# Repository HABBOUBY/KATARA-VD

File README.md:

<div align="center">

# KATARA-VD

### une mahcine qui ne vend pas mais elle donne

Built by **HABBOUBY EDEM**

</div>

---

## Table of Contents

- [About](#about)
- [Repository Structure](#repository-structure)
- [Scope of This Submission](#scope-of-this-submission)
- [Note on Physical Fabrication](#note-on-physical-fabrication)
- [The Story Behind KATARA-VD](#the-story-behind-katara-vd)
- [The Ecosystem: 2 Systems, 1 Mission](#the-ecosystem-2-systems-1-mission)
- [Vending Machine](#vending-machine)
  - [Part 1 — Skeleton, Shelving & Archimedean Dispensers](#part-1--skeleton-shelving--archimedean-dispensers)
  - [Part 2 — Solar Power & Access Doors](#part-2--solar-power--access-doors)
  - [Part 3 — Prescription Verification System](#part-3--prescription-verification-system)
  - [Part 4 — Coin Dispensing Mechanism ("Giving Money")](#part-4--coin-dispensing-mechanism-giving-money)
  - [Part 5 — Coin Acceptance & Storage](#part-5--coin-acceptance--storage)
  - [Part 6 — Charity Keypad PCB](#part-6--charity-keypad-pcb)
  - [Part 7 — Thermal Sensing & Voice Interaction](#part-7--thermal-sensing--voice-interaction)
- [JALOUL — The Restocking Humanoid](#jaloul--the-restocking-humanoid)
  - [Part 8 — Head & Expression System](#part-8--head--expression-system)
  - [Part 9 — Body & Shoulder Joints](#part-9--body--shoulder-joints)
  - [Part 10 — Arm Completion & 360° Gripper](#part-10--arm-completion--360-gripper)
  - [Part 11 — Mecanum Base & Vertical Lift](#part-11--mecanum-base--vertical-lift)
  - [Part 12 — Frame Reinforcement & LiDAR](#part-12--frame-reinforcement--lidar)
- [The Humanitarian Logic — How the Community Fund Works](#the-humanitarian-logic--how-the-community-fund-works)
- [Electronics & PCB](#electronics--pcb)
- [Materials & Fabrication](#materials--fabrication)
- [Fasteners](#fasteners)
- [CAD Files](#cad-files)
- [Simulations](#simulations)
- [On AI Assistance](#on-ai-assistance)
- [Future Improvements](#future-improvements)
- [License](#license)

---

## About

**Katara-vd** une machine intelligente qui donne au lieu de vendre les médiacaments pour les personnes qui ont besoin . et pour que les riches personnes ont accès à cette mahicne ils doivent payer 2 euro , accompagné d'un huamnoid robot qui permet de remplir le distributeur .

Katara-vd  est le projet principal constitué de deux mini -projet:

-le distributeur: qui a une partie pour les médicaments , de plus , ce distributeur a une partie pour les dons qui a un mécanisme de pousse pour donner de l'argent et une petite pièce pour trier les pièces de monnaie ( seulement accepte les pièces de 2 euro)

-The humanoid robot  , son nom est "JALLUL " son tache est de remplir le distributeur lorsqu'il est vide de médicament 

---

## Repository Structure

```text
KATARA-VD/
│
├── 01_3D/
│   ├── SOLIDWORKS_FILES/
│   │   ├── HUMANOID_ROBOT JALOUL/      
│   │   └── VENDING_MACHINE/            
│   ├── STEP_FILES/
│   │   ├── HUMANOID_ROBOT JALOUL/      
│   │   └── VENDING_MACHINE/         
│   └── STL/
│       ├── HUMANOID_ROBOT JALOUL/      
│       └── VENDING_MACHINE/            
│
├── 02_DXF/
│   └── VENDING_MACHINE/
│
├── 03_PCB_DESIGN/
│   ├── VENDING MACHINE PCB.kicad_sch / .kicad_pcb / .kicad_pro / .kicad_prl
│   └── CARTE ELEC MEC 07.step
│
├── 04_DOCS/
│   └── KATARA-VD_PCB_Components.xlsx   
│   └──WIRING
|
├── 05_MEDIA/
│   ├── IMAGES/
│   │   ├── main image of the project.png
│   │   ├── VENDING MACHINE 4K.png
│   │   ├── JALOUL 4K.png
│   │   ├── JALOUL in different positions.png
│   │   └── PCB_KEYBOARD_4K.png
│   └── SIMULATIONS/
│       ├── mechanism of prescription.gif
│       ├── mechanism of giving money.gif
│       ├── GIF MEC PUSHING THE MONEY INTO THE BOX.gif
│       ├── mechanism for opening and closing door.gif
│       └── translation of the robot on yy' axis.gif
│
├── LICENSE
└── README.md
```

---

## remarque pour la fabrication physique 

malheuresemnt j'ai pas accès à l'impression 3d  pour faire un petit prototype et les composants électriques car ils osnt très chères ( raspberry pi 5 and intel real sense)

Mais "KATARA" est pret pour la mettre en production réelle et le rendre fonctionel ( j'ai mis tous les dossiers nécessaires pour l'impression  3d et le découpe cnc)

- **CNC laser-cut MDF** (`02_DXF/`) 
- **3D-printable STL/STEP** (`01_3D/`) 

-une petite remarque: j'ai fait ce mixage de matière  car il y a des pièces qui sont un peu grande donc il est impossible de l'imprimer avec une printer 3D local

---

## Comment l'idée de KATARA est née
Cette idée est née du hackclub comme il est  "charitable " club , donc j'ai pensé à faire une chose qui a des bienfaits pour tous le monde .

---

# Le distributeur 

## Partie 1 : MEC CiSEAUX

Le distributeur a  5 principaux plateaux qui referment les médicaments .Donc pour que les plateaux soient accessibles à "JALOUL"  , doit avoir un mvt en translation donc le mec de ciseux permet les plateaux de sortir autrement dit mec ciseaux permet de  l'étirement et le raccourcissement des plateaux.Ce mec ciseaux est accompagné avec un stepper A17 de telle façon le mvt en rotation se transforme en translation

---

## Partie 2- panneau solaire et le porte intelligent 

AU cas ou les batteries sont vide , et n'existe pas du courant donc il le panneau solaire est un alternatif dans ce cas ( qui permet de charger un batterie et cette batterie va etre consommé au cas ou les batteries vides.
De plus , ce distributeur a une porte intelligente qui s'ouvre et se ferme avec deux vérins électriques d'un façon  à transformer le mvt linéaire en mvt rotatif .Et ça a une dualité de fonction le distributeur n'est pas accessibles aux personnes seulement au "JALLOUL"

---

## Part 3 — Scanner et vérifier l'accès pour les médicaments

Pour avoir un accès légal pour le distributeur , doit etre la personne accompagné avec une ordonnance.Cette etapge est guidé avec un mécanisme linéaire avec un stepper nema A 17 qui permet de translater un support qui a intérieument deux aimants magnétiques de telle façon l'ordonnace est attaché au support avec deux fixation que peut la personnes l'ouvrir et le fermer  ( aussi ces deux fixations ont à son intérieur un aimant magnétique de façon une attraction magnétique va etre crée avec le support principal ).Puis un caméra intelreal sense va détecter  le nom du médicament .Et finalement le médicament est poussé avec un spirale ( avec un moteur pas à pas petit ) puis il tombe en faisant une chute libre.

*A gauche: le mvt linéaire par le stepper et le scan avec le caméra intelreal sense * 
*A droit : le support de l'ordonnance et ses deux fixations  qui vont  l'attatacher *

---

## Part 4 — système de pousse de l'argent

Le premier GIF  montre , le pousse de l'argent pour les donnés aux personnes qui ont besoin 
Le dexième GIF montre aussi le pousse de l'argent mais dans un box , et ce mec est pour conserver les pièces de monnaies que les riches personnes ont donné  dans le boxe  qui sont tombé de la pièce de tri de monnaie 

---

## Part 5 — LA pièce de tri de l'argent 

la pièce de monnaie se glisse d'un façon cette pièce permet de trier les pièces , donc comment ??
Cette pièce a un petit mur qui est oblique d'un 30 degré puis il est suivi  d'un trou  de diamètre un peu plus petit du pièce de monnaie du 2 euro donc si la pièce donné est 2euro va etre glissé  et se tombe dans le box  et il y a un capteur IR qui va détcteer qu'elle a tombé.
Si la pièce est plus petite que 2 euro donc elle va tomber au trou et sort et si elle est plus  grande que 2 euro au début il ne peut pas entrer à cette pièce

regardez l'imagez pour mieux comprendre

---

## Part 6 Clavier PCB pour l'identfication

Chaque personne de la ville ou cette machine est placé a un code  spécifique à lui  , de telle façon le lorsque la personne entre son code il le connait (est ce qu'il a pris 2 euro par jours ou non ? ) ET il y a deux clavier pour les personnes qui ont besoin et son etat financière est  un peu faible et entre les personnes riches . une petite remarque : il existe deux  clavier un peu les dons et un pour les demandes et chaque clavier a aussi un ecran oled
De plus , j'ai fait une petite liste qui renferme tous les composants électriques nécessaires pour réaliser ces claviers

---

## Part 7 — Détection thermique et interaction vocale

Une caméra  infrarouge qui permet de détecter des signes que quelque chose ne va pas de la tristesse ou un état physique  qui demande  une urgence médicale. avec un petit "speaker" intégré qui va répéter des morceaux mp3 pour faire une interaction avec les personnes et le rendre plus dynamique .

---

# JALOUL — the huamnoid robot

## Part 8 — Head & Expression System

la tête du jaloul a un caméra Intel Realsense pour détecter le trajectoire et l'entrainer sur le remplissage du distributeur et lorsqu'il est vide 
et aussi les places exactes à mettre les médicaments.
Aussi jalloul a une bouche mécanique pour le rendre un peu plus réel accompagné avec un sevro moteur MG95
( the metal gear)
A l'intérieur de sa tête il y a raspberry pi 5 pour l'analyse de données et faire bouger aussi la bouche 

---

## Part 9 — Le corps et les articulations du "Jaloul"

"Jaloul" a 12 articulations ( 6 articulations pour chaque main)

la première articulation est dans l'épaule .Puis la bras supérieur à une articulation de façon que l'axe du chaque articulation est orthogonal  à l'autre.Puis une articulation pour le coude et finalement un pour le poignet et une autre pour les doigts .

ces articulations sont suffisantes pour faire les tâches nécessaires 

### le box du médicament 

puisque "JALOUL" a un gripper qui ne peut pas entrer  entre les boxes du médicament  , de telle façon j'ai on va mettre les médicaments espacés pour que jalloul peut les porter avec ses deux "gripper"

## Part 11 — le mvt vertical du jaloul

jaloul  a un mvt vertical grace à un système vis et écrous pour le donner l'accès au tous éatges du distributeur 
ce mvt lineàire est dû à un mvt rotatif d'un moteur stepper nema A17  avec un  accouplement entre le vis et l'axe du moteur ( juste je vais ajouter un petit remarque que le guidage de vis est accompagné avec un roulement à billes radiales en haut )

aussi jalloul a un capteur lidar qui le permet de tracer son trajectoire et détecter aussi les obstacles pour un mieux mvt

de plus jaloul a une base de 4 roues mecanum qui le donne des choix dans mvt comme ça(↑↓←→ )

---

## Electronics & PCB

- **Raspberry Pi 5** — analyse de données
- 
- **Arduino Mega 2560** —carte de commande 
- **Custom KiCad PCB** - le clavier qui permet de connaître chacun avec son identifiant 

voire les composants électriques d'amazon: 
[`04_DOCS/KATARA-VD_PCB_Components.xlsx`](04_DOCS/KATARA-VD_PCB_Components.xlsx).

---

## Materials & Fabrication

| Part type | Material | Fabrication |
|---|---|---|
| Large flat panels (walls, base, shelves) | MDF | CNC laser cutting (`02_DXF/`) |
| Mechanisms & structural parts | ABS | FDM 3D printing |
| Covers & lightweight parts | PLA | FDM 3D printing |

| Setting | Value |
|---------|------|
| Layer Height | 0.20 mm |
| Nozzle | 0.4 mm |
| Infill | 20% |
| Walls | 3 |
| Supports | Only where needed |

---

## Fasteners

| Screw | Length | Quantity |
|-------|-------:|---------:|
| M3 | 20 mm | 40 |
| M3 | 30 mm | 40 |

---

## Simulations

<table>
<tr>
<td width="33%" align="center">

**Prescription mechanism**

Rotary-to-linear extension that presents the prescription to the RealSense camera.

</td>
<td width="33%" align="center">

**Giving money mechanism**

Rack-and-pinion coin ejection, sized to a 1-euro coin.

</td>
<td width="33%" align="center">

**Coin storage**

Donated coins pushed securely into the storage box.

</td>
</tr>
<tr>
<td width="33%" align="center">

**Door actuation**

Dual-actuator, hinge-guided access doors.

</td>
<td width="33%" align="center">

**JALOUL — Y-axis translation**

The backpack lift traveling along the Y-Y′ axis via lead screw.

</td>
<td width="33%" align="center">

**JALOUL — arm reach**

Both arms swept across multiple positions, showing the range unlocked by the extra joints.

</td>
</tr>
</table>

---

##ce que je peux faire dans le future 

-Faire un assemblage et imprimer les pièces  pour faire un petit prototype 
-ajoutez un drone pour transporter les médicaments du l'usine lorsque le stockage est vide

---

## License

**MIT License**.

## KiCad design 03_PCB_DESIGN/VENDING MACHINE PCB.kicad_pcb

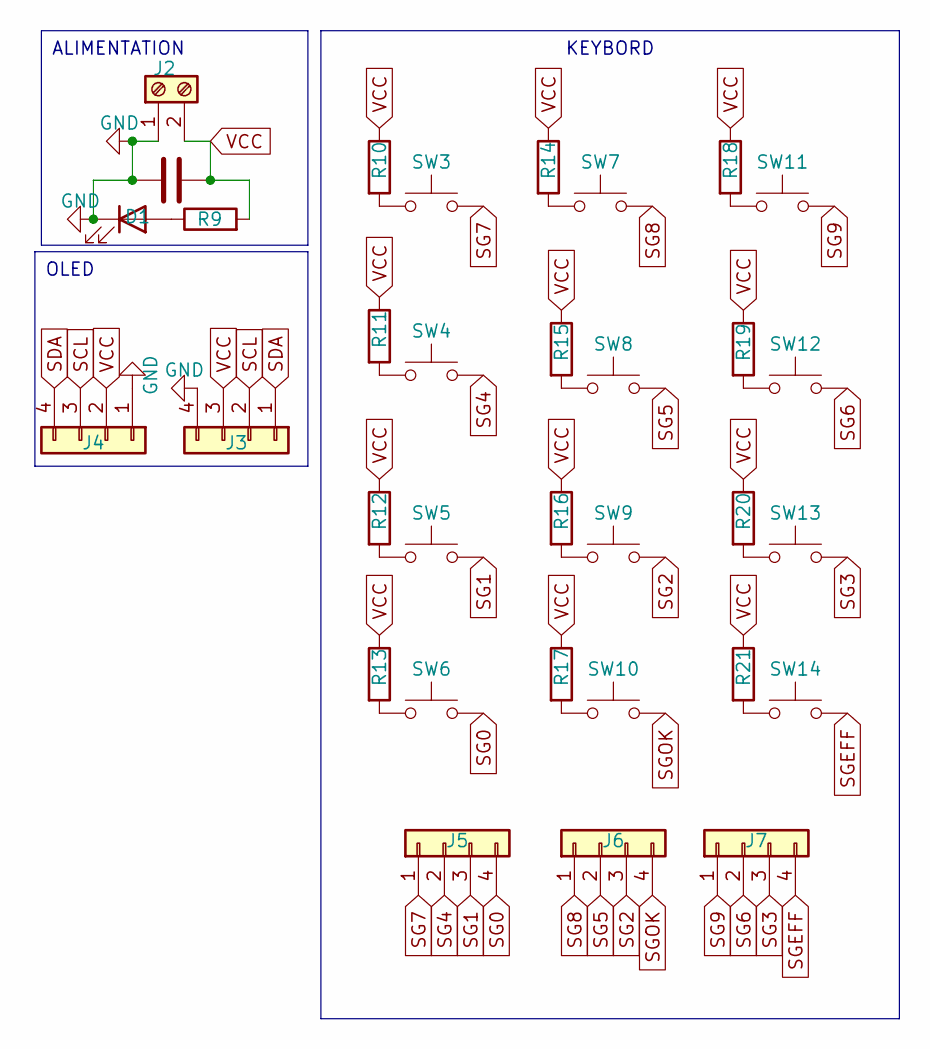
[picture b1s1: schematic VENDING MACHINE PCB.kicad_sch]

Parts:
C1: C; CP_Radial_D4.0mm_P1.50mm
D1: LED; LED_D3.0mm
J2: Screw_Terminal_01x02; TerminalBlock_Phoenix_MKDS-1,5-2_1x02_P5.00mm_Horizontal
J3, J4, J5, J6, J7: Conn_01x04; PinSocket_1x04_P1.27mm_Vertical
R9, R10, R11, R12, R13, R14, R15, R16, R17, R18, R19, R20, R21: R; R_Axial_DIN0204_L3.6mm_D1.6mm_P5.08mm_Horizontal
SW3, SW4, SW5, SW6, SW7, SW8, SW9, SW10, SW11, SW12, SW13, SW14: SW_Push; SW_Push_1P1T_NO_CK_KSC6xxG

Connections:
GND: C1.2, D1.1 (K), J2.1, J3.4, J4.1
unnamed: D1.2 (A), R9.1
unnamed: R10.2, SW3.1
unnamed: R11.2, SW4.1
unnamed: R12.2, SW5.1
unnamed: R13.2, SW6.1
unnamed: R14.2, SW7.1
unnamed: R15.2, SW8.1
unnamed: R16.2, SW9.1
unnamed: R17.2, SW10.1
unnamed: R18.2, SW11.1
unnamed: R19.2, SW12.1
unnamed: R20.2, SW13.1
unnamed: R21.2, SW14.1
SCL: J3.2, J4.3
SDA: J3.1, J4.4
SG0: J5.4, SW6.2
SG1: J5.3, SW5.2
SG2: J6.3, SW9.2
SG3: J7.3, SW13.2
SG4: J5.2, SW4.2
SG5: J6.2, SW8.2
SG6: J7.2, SW12.2
SG7: J5.1, SW3.2
SG8: J6.1, SW7.2
SG9: J7.1, SW11.2
SGEFF: J7.4, SW14.2
SGOK: J6.4, SW10.2
VCC: C1.1, J2.2, J3.3, J4.2, R9.2, R10.1, R11.1, R12.1, R13.1, R14.1, R15.1, R16.1, R17.1, R18.1, R19.1, R20.1, R21.1

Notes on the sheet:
ALIMENTATION
KEYBORD
OLED

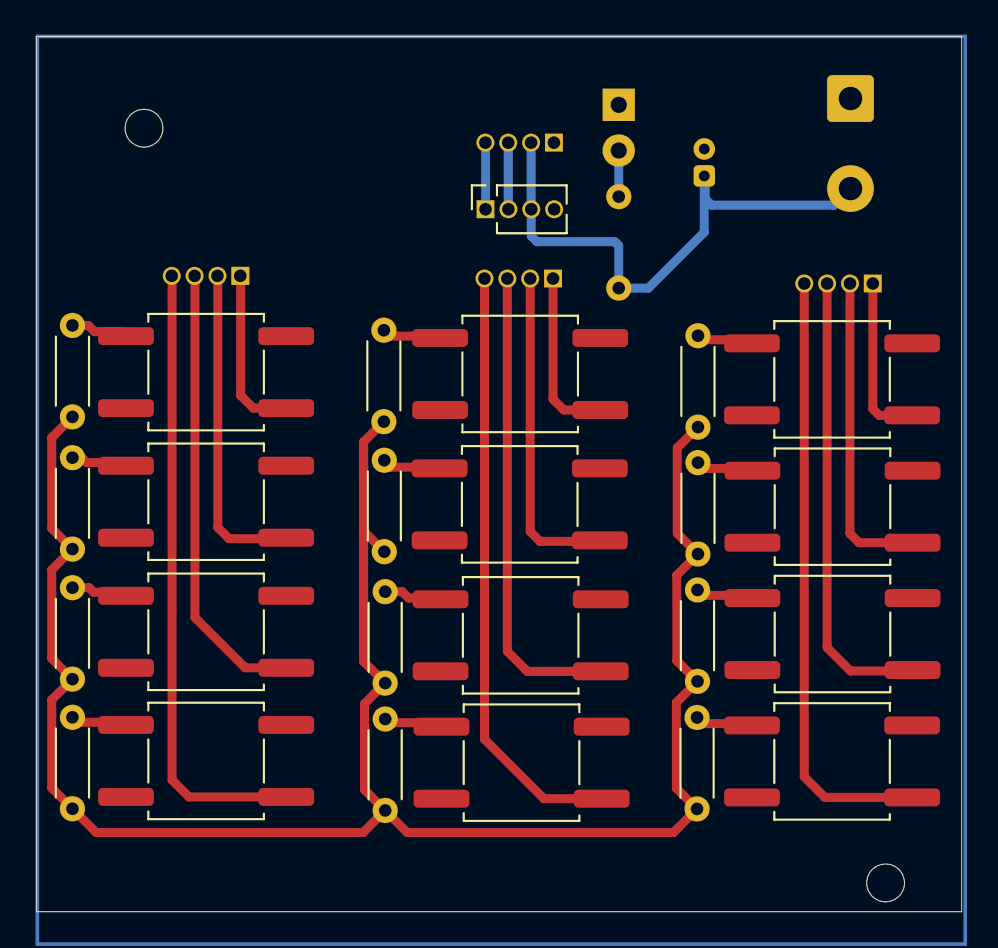
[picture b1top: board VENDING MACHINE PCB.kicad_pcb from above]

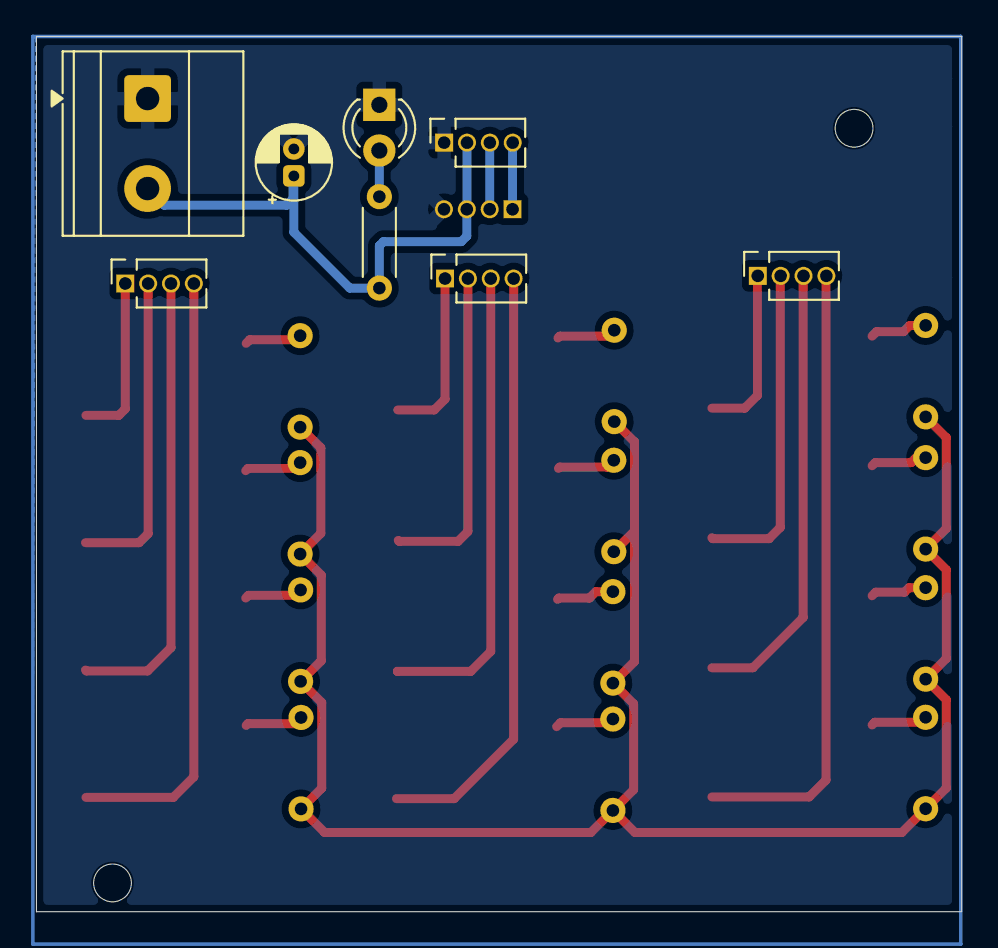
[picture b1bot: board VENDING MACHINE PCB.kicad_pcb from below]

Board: 2 copper layers, 51.4 x 48.6 mm, 33 parts (8 on the bottom side), 29 nets.
